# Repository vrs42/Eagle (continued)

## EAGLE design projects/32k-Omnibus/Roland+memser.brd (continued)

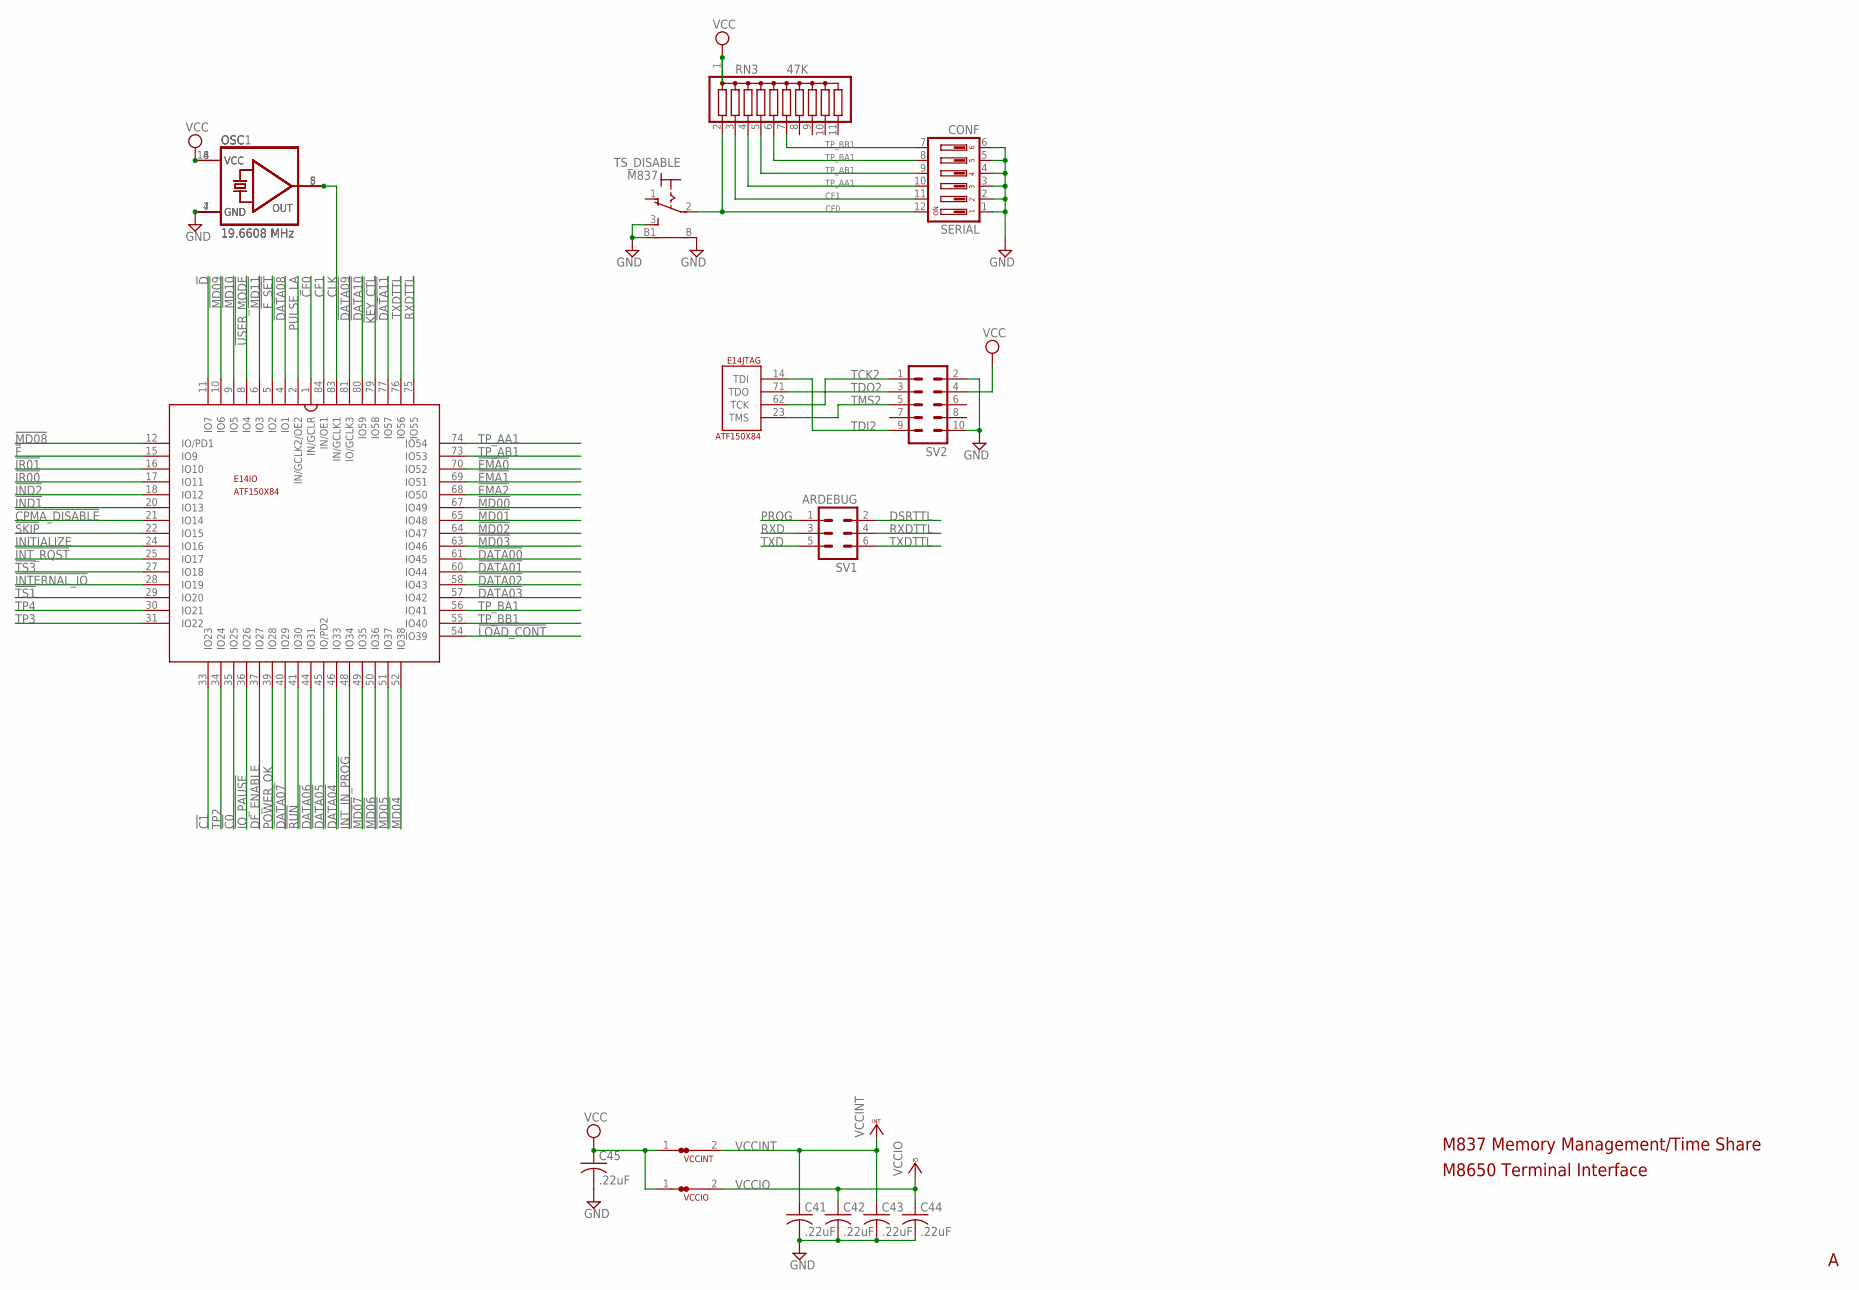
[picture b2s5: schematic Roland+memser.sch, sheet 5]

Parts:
C41, C42, C43, C44, C45: .22uF; C063-025X075
E14: ATF150X84; S84
OSC: 19.6608 MHz; DIL08S
OSC1: 19.6608 MHz; DIL14S
RN3: 47K; SIL11
SERIAL: CONF; DP-06
SV1: ARDEBUG; MA03-2
SV2: ML10
TS_DISABLE: M837; 9070-1W
VCCINT: JUMPER-NC1; NC1
VCCIO: JUMPER-NC1; NC1

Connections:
!C0: E14.35 (IO25); also elsewhere on the board
!C1: E14.33 (IO23); also elsewhere on the board
!CPMA_DISABLE: E14.21 (IO14); also elsewhere on the board
!D: E14.11 (IO7); also elsewhere on the board
!DATA00: E14.61 (IO45); also elsewhere on the board
!DATA01: E14.60 (IO44); also elsewhere on the board
!DATA02: E14.58 (IO43); also elsewhere on the board
!DATA03: E14.57 (IO42); also elsewhere on the board
!DATA04: E14.46 (IO33); also elsewhere on the board
!DATA05: E14.45 (IO/PD2); also elsewhere on the board
!DATA06: E14.44 (IO31); also elsewhere on the board
!DATA07: E14.40 (IO29); also elsewhere on the board
!DATA08: E14.4 (IO1); also elsewhere on the board
!DATA09: E14.81 (IO/GCLK3); also elsewhere on the board
!DATA10: E14.80 (IO59); also elsewhere on the board
!DATA11: E14.77 (IO57); also elsewhere on the board
!EMA0: E14.70 (IO52); also elsewhere on the board
!EMA1: E14.69 (IO51); also elsewhere on the board
!EMA2: E14.68 (IO50); also elsewhere on the board
!F: E14.15 (IO9); also elsewhere on the board
!F_SET: E14.5 (IO2); also elsewhere on the board
!IND1: E14.20 (IO13); also elsewhere on the board
!IND2: E14.18 (IO12); also elsewhere on the board
!INTERNAL_IO: E14.28 (IO19); also elsewhere on the board
!INT_IN_PROG: E14.48 (IO34); also elsewhere on the board
!INT_RQST: E14.25 (IO17); also elsewhere on the board
!IO_PAUSE: E14.36 (IO26); also elsewhere on the board
!IR00: E14.17 (IO11); also elsewhere on the board
!IR01: E14.16 (IO10); also elsewhere on the board
!KEY_CTL: E14.79 (IO58); also elsewhere on the board
!LOAD_CONT: E14.54 (IO39); also elsewhere on the board
!MD00: E14.67 (IO49); also elsewhere on the board
!MD01: E14.65 (IO48); also elsewhere on the board
!MD02: E14.64 (IO47); also elsewhere on the board
!MD03: E14.63 (IO46); also elsewhere on the board
!MD04: E14.52 (IO38); also elsewhere on the board
!MD05: E14.51 (IO37); also elsewhere on the board
!MD06: E14.50 (IO36); also elsewhere on the board
!MD07: E14.49 (IO35); also elsewhere on the board
!MD08: E14.12 (IO/PD1); also elsewhere on the board
!MD09: E14.10 (IO6); also elsewhere on the board
!MD10: E14.9 (IO5); also elsewhere on the board
!MD11: E14.6 (IO3); also elsewhere on the board
!RUN: E14.41 (IO30); also elsewhere on the board
!SKIP: E14.22 (IO15); also elsewhere on the board
!TS1: E14.29 (IO20); also elsewhere on the board
!TS3: E14.27 (IO18); also elsewhere on the board
!USER_MODE: E14.8 (IO4); also elsewhere on the board
CF0: E14.1 (IN/GCLR), RN3.2, SERIAL.12, TS_DISABLE.2
CF1: E14.84 (IN/OE1), RN3.3, SERIAL.11
CLK: E14.83 (IN/GCLK1), OSC.5 (OUT), OSC1.8 (OUT)
DF_ENABLE: E14.37 (IO27); also elsewhere on the board
DSRTTL: SV1.2; also elsewhere on the board
GND: C41.2, C42.2, C43.2, C44.2, C45.2, E14.7 (GND), E14.19 (GND), E14.32 (GND), E14.42 (GND), E14.47 (GND), E14.59 (GND), E14.72 (GND), E14.82 (GND), OSC.4 (GND), OSC1.7 (GND), SERIAL.1, SERIAL.2, SERIAL.3, SERIAL.4, SERIAL.5, SERIAL.6, SV2.2, SV2.10, TS_DISABLE.3 (S), TS_DISABLE.B, TS_DISABLE.B1; also elsewhere on the board
INITIALIZE: E14.24 (IO16); also elsewhere on the board
POWER_OK: E14.39 (IO28); also elsewhere on the board
PROG: SV1.1; also elsewhere on the board
PULSE_LA: E14.2 (IN/GCLK2/OE2); also elsewhere on the board
RXD: SV1.3; also elsewhere on the board
RXDTTL: E14.75 (IO55), SV1.4; also elsewhere on the board
TCK2: E14.62 (TCK), SV2.1
TDI2: E14.14 (TDI), SV2.9
TDO2: E14.71 (TDO), SV2.3
TMS2: E14.23 (TMS), SV2.5
TP2: E14.34 (IO24); also elsewhere on the board
TP3: E14.31 (IO22); also elsewhere on the board
TP4: E14.30 (IO21); also elsewhere on the board
TP_AA1: E14.74 (IO54), RN3.4, SERIAL.10; also elsewhere on the board
TP_AB1: E14.73 (IO53), RN3.5, SERIAL.9; also elsewhere on the board
TP_BA1: E14.56 (IO41), RN3.6, SERIAL.8; also elsewhere on the board
TP_BB1: E14.55 (IO40), RN3.7, SERIAL.7; also elsewhere on the board
TXD: SV1.5; also elsewhere on the board
TXDTTL: E14.76 (IO56), SV1.6; also elsewhere on the board
VCC: C45.1, OSC.8 (VCC), OSC1.14 (VCC), RN3.1, SV2.4, VCCINT.1, VCCIO.1; also elsewhere on the board
VCCINT: C41.1, C43.1, E14.3 (VCCINT), E14.43 (VCCINT), VCCINT.2
VCCIO: C42.1, C44.1, E14.13 (VCCIO), E14.26 (VCCIO), E14.38 (VCCIO), E14.53 (VCCIO), E14.66 (VCCIO), E14.78 (VCCIO), VCCIO.2

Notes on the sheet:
M837 Memory Management/Time Share
M8650 Terminal Interface

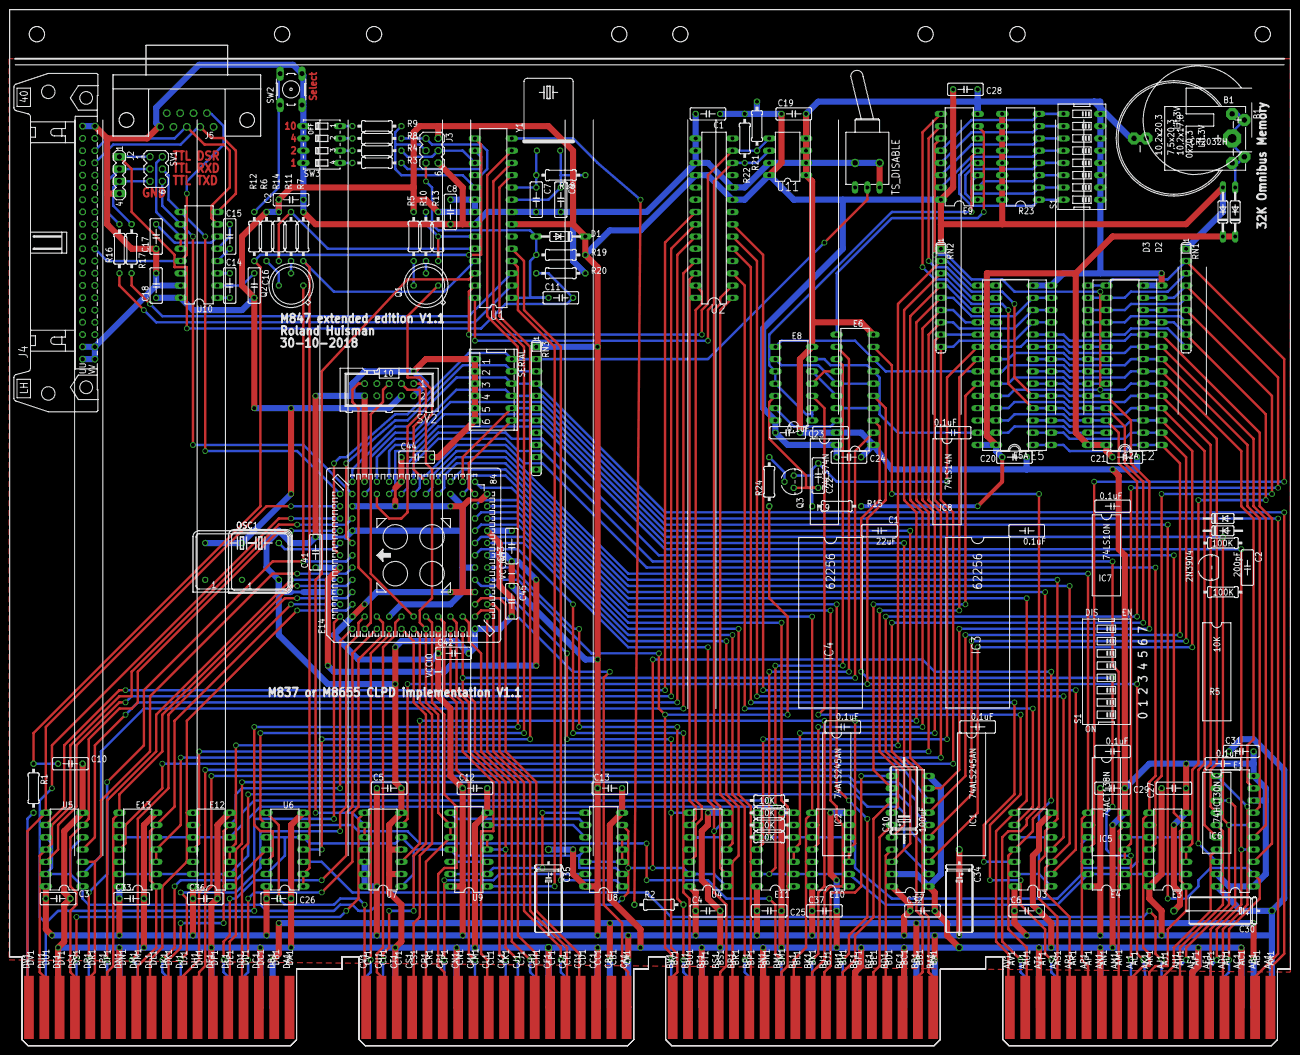
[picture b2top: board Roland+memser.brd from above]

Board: 2 copper layers, 265.3 x 214.6 mm, 121 parts (0 on the bottom side), 214 nets.
